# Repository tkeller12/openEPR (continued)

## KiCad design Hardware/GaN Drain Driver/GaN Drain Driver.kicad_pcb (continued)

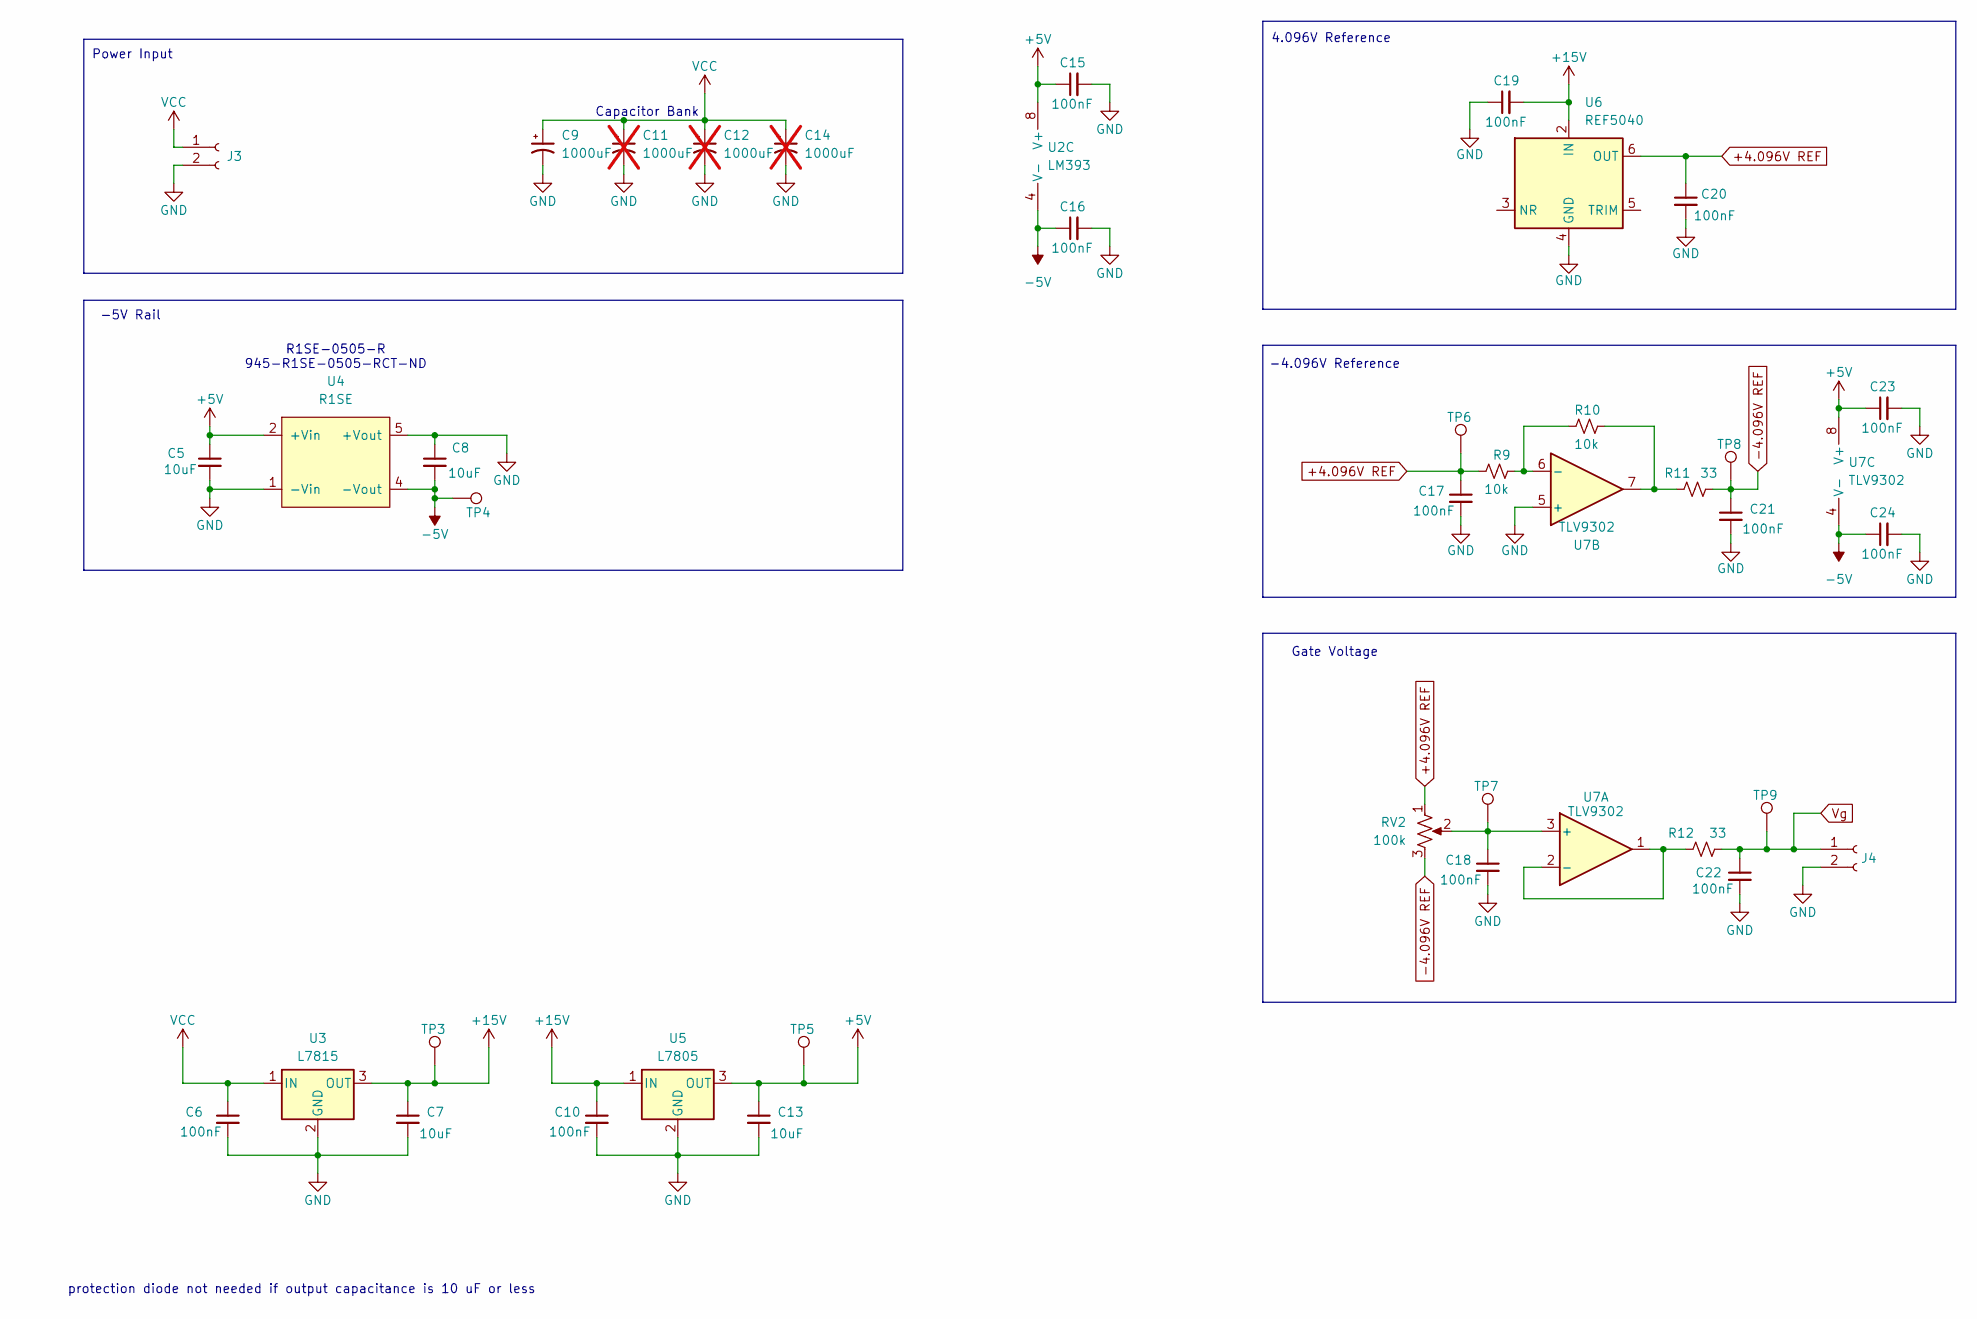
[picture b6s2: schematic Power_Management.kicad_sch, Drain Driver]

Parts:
C5, C7, C8, C13: 10uF; C_0805_2012Metric; MPN CL21A106KAYNNNE; Digikey 1276-2891-1-ND
C6, C10, C15, C16, C17, C18, C19, C20, C21, C22, C23, C24: 100nF; C_0805_2012Metric; MPN KGM21NR71H104KT; Digikey 478-KGM21NR71H104KTCT-ND
C9: 1000uF; CP_Radial_D13.0mm_P5.00mm; MPN UCY2C101MHD1TO; Digikey 493-4784-1-ND
C11, C12, C14: 1000uF; CP_Radial_D13.0mm_P5.00mm; MPN UCY2C101MHD1TO; Digikey 493-4784-1-ND; not fitted
J3, J4: 0022272021; Molex_KK-254_AE-6410-02A_1x02_P2.54mm_Vertical; MPN 0022272021; Digikey WM4111-ND
R9, R10: 10k; R_0805_2012Metric; MPN CRCW080510K0FKEAC; Digikey 541-3976-1-ND
R11, R12: 33; R_0805_2012Metric; MPN RC0805FR-0733RL; Digikey 311-33.0CRCT-ND
RV2: 100k; Potentiometer_Bourns_3296W_Vertical; MPN PV36W104C01B00; Digikey 118-PV36W104C01B00-ND
TP3, TP4, TP5, TP6, TP7, TP8, TP9: TestPoint; TestPoint_Pad_D1.0mm
U2: LM393; SOIC-8_3.9x4.9mm_P1.27mm; MPN LM393DT; Digikey 497-1593-1-ND
U3: L7815; TO-252-2; MPN MC78M15CDTG; Digikey MC78M15CDTGOS-ND
U4: R1SE; R1SE_SMD5_12.75X10.7X6.7_SINGLE_RCP; MPN R1SE-0505-R; Digikey 945-R1SE-0505-RCT-ND
U5: L7805; TO-252-2; MPN MC7805BDTRKG; Digikey MC7805BDTRKGOSCT-ND
U6: REF5040; SOIC-8_3.9x4.9mm_P1.27mm; MPN REF5040AIDR; Digikey 296-46190-1-ND
U7: TLV9302; SOIC-8_3.9x4.9mm_P1.27mm; MPN TLV9302IDR; Digikey 296-53513-1-ND

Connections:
+4.096V REF: C17.1, C20.1, R9.1, RV2.1, TP6.1, U6.6 (OUT); also elsewhere on the board
+5V: C5.1, C13.1, C15.1, C23.1, TP5.1, U2.8 (V+), U4.2 (+Vin), U5.3 (OUT), U7.8 (V+); also elsewhere on the board
+15V: C7.1, C10.1, C19.2, TP3.1, U3.3 (OUT), U5.1 (IN), U6.2 (IN); also elsewhere on the board
-4.096V REF: C21.1, R11.2, RV2.3, TP8.1; also elsewhere on the board
-5V: C8.2, C16.1, C24.1, TP4.1, U2.4 (V-), U4.4 (-Vout), U7.4 (V-)
GND: C5.2, C6.2, C7.2, C8.1, C9.2, C10.2, C11.2, C12.2, C13.2, C14.2, C15.2, C16.2, C17.2, C18.2, C19.1, C20.2, C21.2, C22.2, C23.2, C24.2, J3.2, J4.2, U3.2 (GND), U4.1 (-Vin), U4.5 (+Vout), U5.2 (GND), U6.4 (GND), U7.5 (+); also elsewhere on the board
unnamed: R10.2, R11.1, U7.7
unnamed: C18.1, RV2.2, TP7.1, U7.3 (+)
unnamed: R12.1, U7.1, U7.2 (-)
unnamed: R9.2, R10.1, U7.6 (-)
VCC: C6.1, C9.1, C11.1, C12.1, C14.1, J3.1, U3.1 (IN); also elsewhere on the board
Vg: C22.1, J4.1, R12.2, TP9.1; also elsewhere on the board

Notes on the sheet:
R1SE-0505-R 945-R1SE-0505-RCT-ND
protection diode not needed if output capacitance is 10 uF or less
-5V Rail
Gate Voltage
4.096V Reference
Capacitor Bank
Power Input
-4.096V Reference

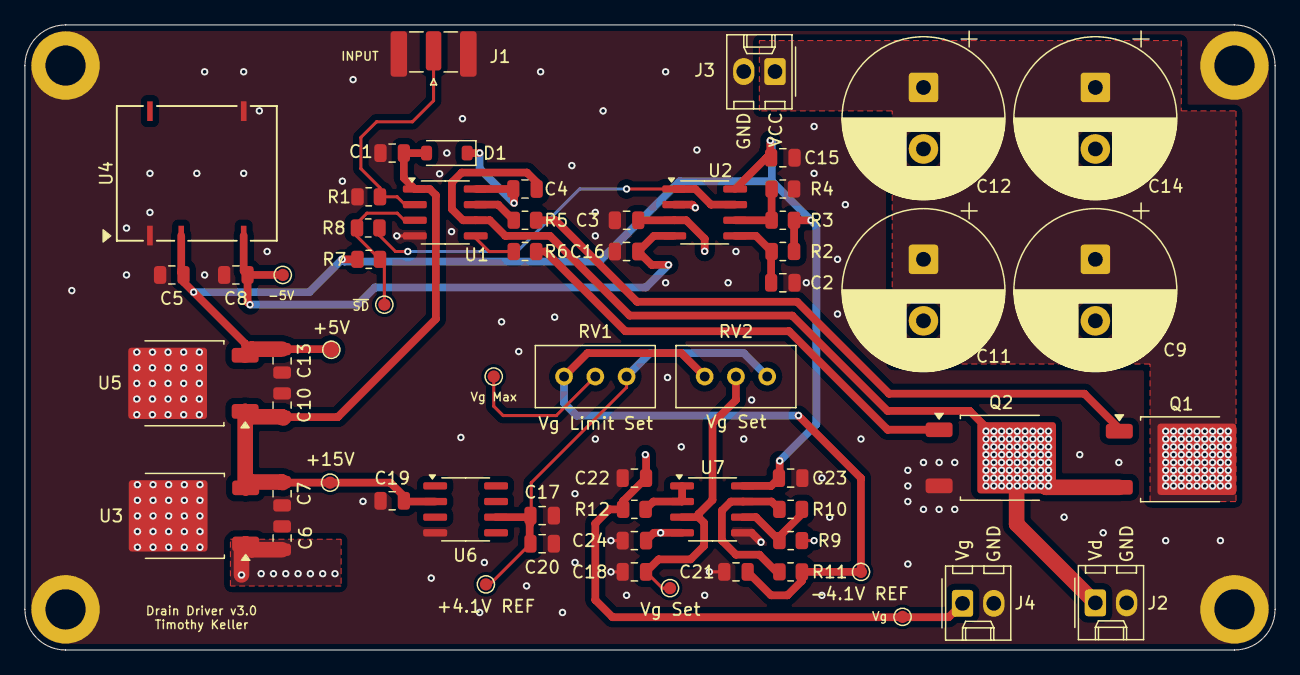
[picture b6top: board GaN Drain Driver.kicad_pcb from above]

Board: 4 copper layers, 101.6 x 50.8 mm, 65 parts (0 on the bottom side), 24 nets.

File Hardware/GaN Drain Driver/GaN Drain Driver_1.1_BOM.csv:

"Reference","Value","Footprint","Qty","DNP","Digikey","Manufacturer","MPN","Description"
"C1,C3,C4,C6,C10,C15,C16,C17,C18,C19,C20,C21,C22,C23,C24","100nF","Capacitor_SMD:C_0805_2012Metric","15","","478-KGM21NR71H104KTCT-ND","KYOCERA AVX","KGM21NR71H104KT","CAP CER 0.1UF 50V X7R 0805"
"C2,C5,C7,C8,C13","10uF","Capacitor_SMD:C_0805_2012Metric","5","","1276-2891-1-ND","Samsung Electro-Mechanics","CL21A106KAYNNNE","CAP CER 10UF 25V X5R 0805"
"C9","1000uF","Capacitor_THT:CP_Radial_D13.0mm_P5.00mm","1","","493-4784-1-ND","Nichicon","UCY2C101MHD1TO","CAP ALUM 100UF 20% 160V RADIAL"
"C11,C12,C14","1000uF","Capacitor_THT:CP_Radial_D13.0mm_P5.00mm","3","DNP","493-4784-1-ND","Nichicon","UCY2C101MHD1TO","CAP ALUM 100UF 20% 160V RADIAL"
"D1","1N5819HW-7-F","Diode_SMD:D_SOD-123","1","","1N5819HW-FDICT-ND","Diodes Incorporated","1N5819HW-7-F","DIODE SCHOTTKY 40V 1A SOD123"
"J1","SMA-J-P-H-ST-EM1","Connector_Coaxial:SMA_Samtec_SMA-J-P-X-ST-EM1_EdgeMount","1","","SAM8857-ND","Samtec Inc.","SMA-J-P-H-ST-EM1","CONN SMA JACK STR 50OHM EDGE MNT"
"J2,J3,J4","Conn_01x02_Socket","Connector_Molex:Molex_KK-254_AE-6410-02A_1x02_P2.54mm_Vertical","3","","WM4111-ND","Molex","0022272021","CONN HEADER VERT 2POS 2.54MM"
"Q1,Q2","NVD360N65S3T4G","Package_TO_SOT_SMD:TO-252-2","2","","488-NVD360N65S3T4GCT-ND","onsemi","NVD360N65S3T4G","SF3 EASY AUTO 360MOHM DPAK"
"R1,R2,R3,R4,R7,R9,R10","10k","Resistor_SMD:R_0805_2012Metric","7","","541-3976-1-ND","Vishay Dale","CRCW080510K0FKEAC","RES 10K OHM 1% 1/8W 0805"
"R5,R6,R11,R12","33","Resistor_SMD:R_0805_2012Metric","4","","311-33.0CRCT-ND","YAGEO","RC0805FR-0733RL","RES 33 OHM 1% 1/8W 0805"
"RV1,RV2","100k","Potentiometer_THT:Potentiometer_Bourns_3296W_Vertical","2","","118-PV36W104C01B00-ND","Bourns Inc.","PV36W104C01B00","TRIMMER 100K OHM 0.5W PC PIN TOP"
"U1","IRS2008S","Package_SO:SOIC-8_3.9x4.9mm_P1.27mm","1","","IRS2008STRPBFCT-ND","Infineon Technologies","IRS2008STRPBF","IC GATE DRVR HALF-BRIDGE 8SOIC"
"U2","LM393","Package_SO:SOIC-8_3.9x4.9mm_P1.27mm","1","","497-1593-1-ND","STMicroelectronics","LM393DT","IC COMPARATOR 2 GEN PUR 8SOIC"
"U3","L7815","Package_TO_SOT_SMD:TO-252-2","1","","MC78M15CDTGOS-ND","onsemi","MC78M15CDTG","IC REG LINEAR 15V 500MA DPAK"
"U4","R1SE","_tim-DC-DC:R1SE_SMD5_12.75X10.7X6.7_SINGLE_RCP","1","","945-R1SE-0505-RCT-ND","Recom Power","R1SE-0505-R","DC DC CONVERTER 5V 1W"
"U5","L7805","Package_TO_SOT_SMD:TO-252-2","1","","MC7805BDTRKGOSCT-ND","onsemi","MC7805BDTRKG","IC REG LINEAR 5V 1A DPAK"
"U6","REF5040","Package_SO:SOIC-8_3.9x4.9mm_P1.27mm","1","","296-46190-1-ND","Texas Instruments","REF5040AIDR","IC VREF SERIES 0.1% 8SOIC"
"U7","TLV9302","Package_SO:SOIC-8_3.9x4.9mm_P1.27mm","1","","296-53513-1-ND","Texas Instruments","TLV9302IDR","Dual Low-Voltage Rail-to-Rail Output Operational Amplifiers, SOIC-8/SSOP-8"

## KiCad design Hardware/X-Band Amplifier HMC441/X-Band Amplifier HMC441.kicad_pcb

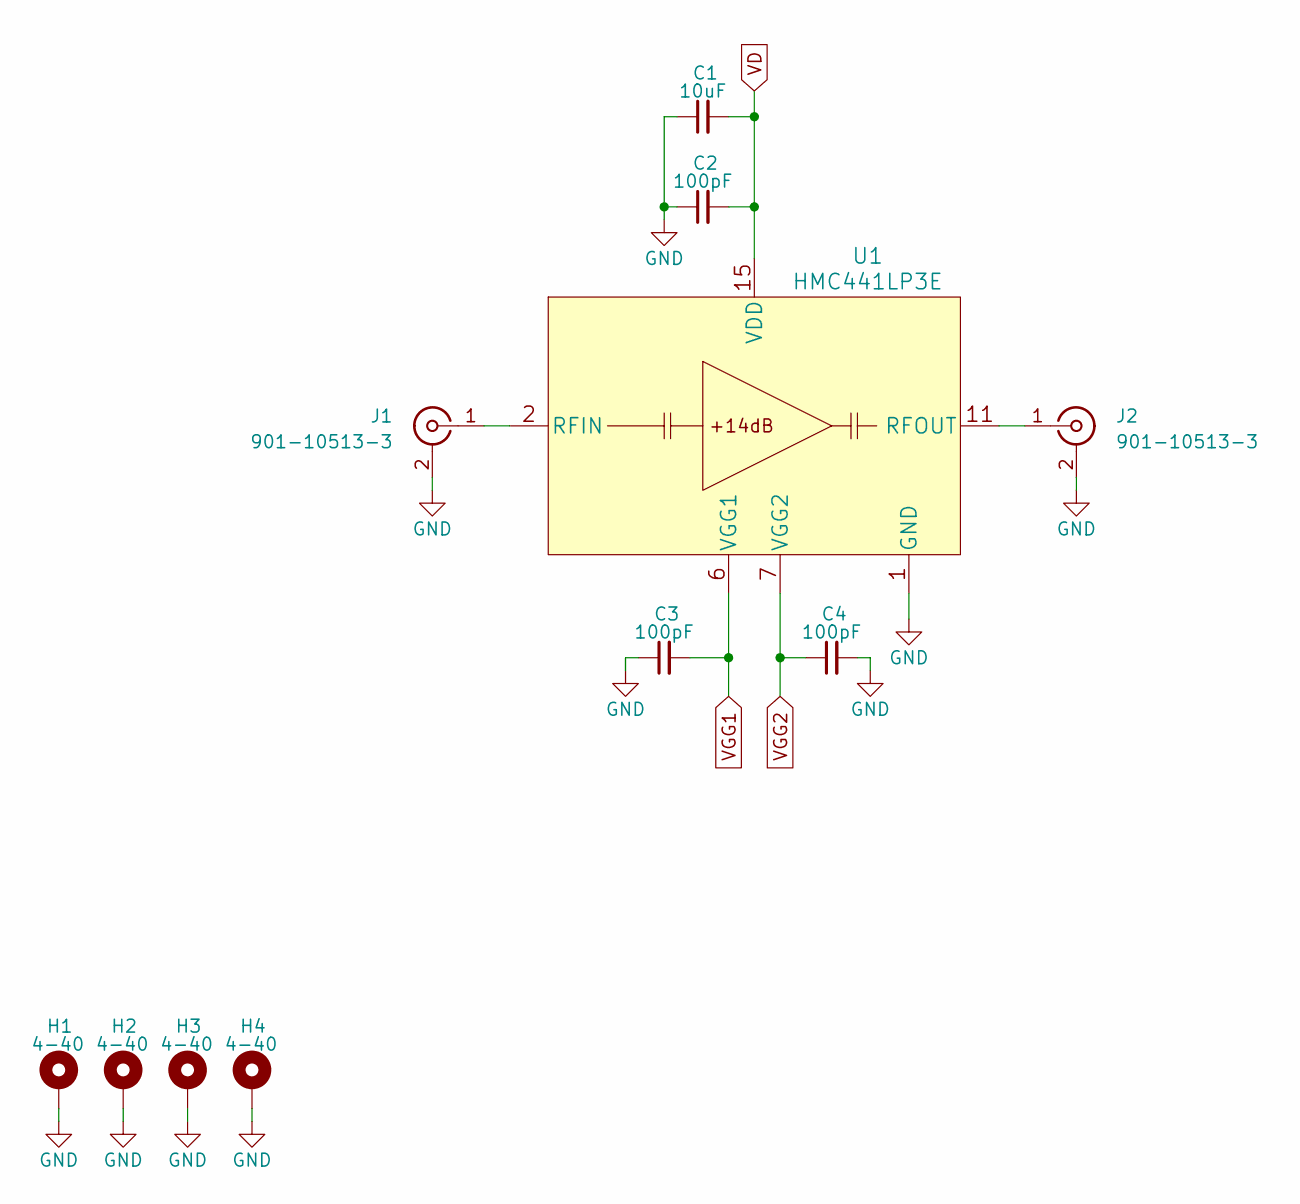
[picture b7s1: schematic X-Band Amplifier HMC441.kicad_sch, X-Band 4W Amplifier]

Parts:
C1: 10uF; C_0805_2012Metric
C2, C3, C4: 100pF; C_0402_1005Metric
H1, H2, H3, H4: 4-40; 4-40_Hole_Pad
J1, J2: 901-10513-3; AMPHENOL_901-10513-3_EDGE_LAUNCH_Female
U1: HMC441LP3E; HMC441LP3ETR

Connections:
GND: C1.1, C2.1, C3.1, C4.2, H1.1, H2.1, H3.1, H4.1, J1.2 (Ext), J2.2 (Ext), U1.1 (GND), U1.3 (GND), U1.4 (GND), U1.5 (GND), U1.8 (GND), U1.9 (GND), U1.10 (GND), U1.12 (GND), U1.13 (GND), U1.14 (GND), U1.16 (GND), U1.17 (GND)
unnamed: J1.1 (In), U1.2 (RFIN)
unnamed: J2.1 (In), U1.11 (RFOUT)
VD: C1.2, C2.2, U1.15 (VDD)
VGG1: C3.2, U1.6 (VGG1)
VGG2: C4.1, U1.7 (VGG2)

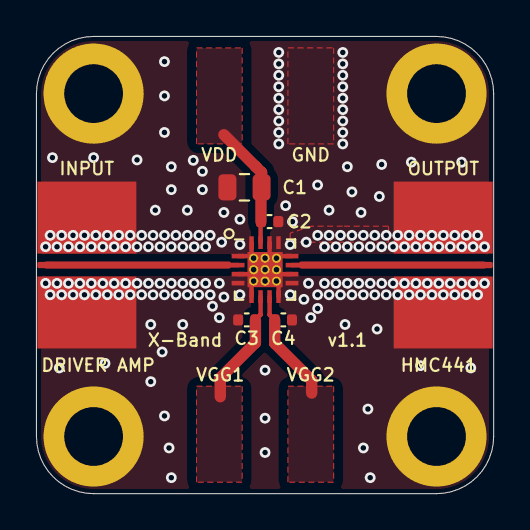
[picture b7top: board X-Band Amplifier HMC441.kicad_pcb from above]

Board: 4 copper layers, 25.4 x 25.4 mm, 11 parts (0 on the bottom side), 6 nets.

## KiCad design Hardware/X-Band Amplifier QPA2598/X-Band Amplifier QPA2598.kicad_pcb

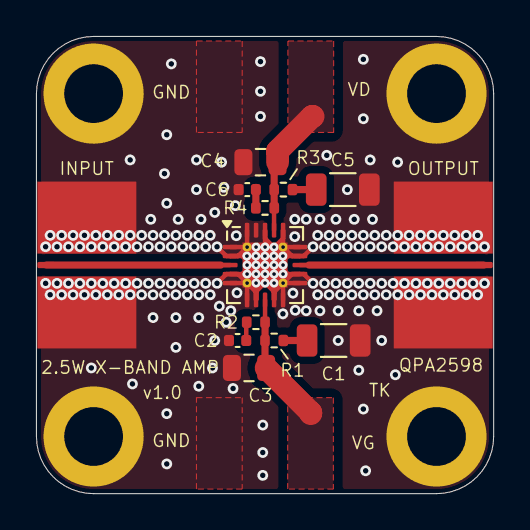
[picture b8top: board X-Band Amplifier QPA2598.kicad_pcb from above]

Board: 4 copper layers, 25.4 x 25.4 mm, 17 parts (0 on the bottom side), 9 nets.

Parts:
C1, C5: 10uF; C_1206_3216Metric
C2, C6: 1nF; C_0402_1005Metric
C3, C4: 10uF; C_0805_2012Metric
H1, H2, H3, H4: 4-40; 4-40_Hole_Pad
J1, J2: 901-10513-3; AMPHENOL_901-10513-3_EDGE_LAUNCH_Female
R1, R3: 0; R_0402_1005Metric
R2, R4: 1.8; R_0402_1005Metric
U1: QPA2598; QFN-20-1EP_4x4mm_P0.5mm_EP2.5x2.5mm_ThermalVias

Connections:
GND: C1.1, C2.1, C3.1, C4.2, C5.2, C6.2, H1.1, H2.1, H3.1, H4.1, J1.2 (Ext), J2.2 (Ext), U1.1 (NC), U1.2 (NC), U1.4 (NC), U1.5 (NC), U1.6 (NC), U1.7 (NC), U1.9 (NC), U1.10 (NC), U1.11 (NC), U1.12 (NC), U1.14 (NC), U1.15 (NC), U1.16 (NC), U1.18 (NC), U1.19 (NC), U1.20 (NC), U1.21 (GND)
unnamed: C1.2, R1.1
unnamed: C2.2, R2.1
unnamed: C5.1, R3.2
unnamed: C6.1, R4.2
unnamed: J1.1 (In), U1.3 (RF_IN)
unnamed: J2.1 (In), U1.13 (RF_OUT)
VD: C4.1, R3.1, R4.1, U1.17 (VD)
VG: C3.2, R1.2, R2.2, U1.8 (VG)

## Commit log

2023-05-21 Adding KiCAD project for L-Band Bridge
2023-05-21 Updating L-Band Bridge Schematic
2023-05-27 Updates to L-Band Bridge
2023-05-29 Backups
2023-06-03 L-Band Bridge Schematic Updates
    Assigning footprints
2023-06-03 Adding gitignore
2023-06-03 Starting development of GUI for acquisition
2023-06-12 Updating Schematic
    Removed Power Divider
    Removed Op Amp on IF output
2023-07-30 Removing Filter and IF Amp
2023-07-30 Working on BOM
2023-08-19 Creating new schematic for S-band transceiver
2023-08-20 Added receiver bypass switch comment
2024-02-17 Adding notes to S-band transceiver
2024-03-01 Updates to Schematic
2024-03-02 Working on schematic for adf4351
2024-03-03 Updating schematic
2024-03-05 Updates to receiver
2024-03-06 Updates to power supply schematic
2024-03-07 Changes to schematic
2024-03-12 Updating microcontroller schematic
2024-03-13 Updating PLL
2024-03-16 Finished assigning footprints and starting board layout
2024-03-16 Fixed issue with limiter footprint
2024-03-16 Updating Capacitors and LEDs in schematic
2024-03-16 Updating synthesizer schematic and layout
2024-03-16 Updates to synthesizer layout
2024-03-16 Updating board layout, adding inductor to LNA input
2024-03-17 Starting to route board
2024-03-17 Routing board
2024-03-17 Updating board layout and routing
2024-03-17 Routing microcontroller
2024-03-17 Updating routing
2024-03-17 Updating silkscreen
2024-03-17 Cleaning up silkscreen
2024-03-17 Removing solder mask from coplanar waveguide traces
2024-03-17 Updates to Board
2024-03-18 Updating notes in schematic
2024-03-18 Adding gerbers for v1.0
2024-03-18 Minor Changes
2024-03-19 Updates to BOM
2024-03-23 Adding firmware for S-Band Transceiver
2024-03-23 Adding library files
2024-03-24 updating values
2024-03-24 Updating BOM
2024-03-24 Adding ADC library and serial commands
2024-03-24 Updating platform io settings
2024-03-24 Adding library for digital phase shifter
2024-03-24 Cleaning up code
2024-03-25 Fixing bug in firmware with TX and RX Amp enable
2024-03-26 Fixing bug with RUN LED
2024-03-26 Fixed bug with ADC readings
    Need to remove TX AMP Enable
2024-03-26 Defined RUN LED delay
2024-03-26 Updating python script
2024-03-26 Testing manually setting PIN_B5 to output
2024-03-26 updating frequency range of sweep default values
2024-03-26 Fixing issues in schematic
2024-03-26 Fixed issue with tx amp enable added new serial commands
2024-03-27 Fixing issue with phase shifter schematic
2024-03-27 Minor change to script
2024-03-28 Adding serial command for lock detect
2024-03-28 minor changes to script
2024-03-30 Updating SPI mode for Phase shifter IC
2024-03-30 Updating python phase function
2024-03-30 Creating python package for controlling S-band transceiver
2024-03-31 Adding new script for tuning
2024-04-04 Adding bridge controller schematic
2024-04-05 Updating bridge controller
2024-04-06 Updates to Bridge controller
2024-04-15 Updating DAQ
2024-04-18 Updates to DAQ board layout
2024-04-19 Fixed DRC errors on Board
2024-04-19 Need to update TX/RX level for UART communication
2024-04-19 Updating FTDI controller for +5V RX and TX
2024-04-19 Finalizing Board Routing
2024-04-20 Minor Updates to Board
2024-04-20 Adding gerbers
2024-04-25 Adding S-Band Amplifier project
2024-04-27 Updating Amplifier board
2024-04-27 Finalizing Amplifier Board
2024-04-28 Adding gerbers for S-band amplifier
2024-05-01 Fixing issue with Silkscreen on PCB
2024-05-01 Incrementing Board Version
2024-05-02 Updating tune script
2024-05-02 Auto stash before merge of "master" and "origin/master"
2024-05-02 Updating DAQ board schematic
2024-05-02 Updates to DAQ
2024-05-02 Adding CAD model for PCB and heat spreader
2024-05-05 Adding S-Band Driver Amplifier
2024-05-05 Updating Schematic and Board
2024-05-05 Generated Gerbers for S-Band Driver Amp
2024-05-09 Updating script to set parameters
2024-05-09 Adding decoupling capacitor
2024-05-10 adding calibration script
2024-05-10 Adding script for calibration data
2024-05-12 adding new project for PFU
2024-05-14 Updating schematic for PFU
2024-06-04 Updating parameters setting script
2024-06-04 Adding phase function WIP
2024-06-04 Testing phase, not currently working
2024-06-04 Testing divided feedback
2024-06-04 more testing...
2024-06-04 Working example
    register 5 must be 0x5A0005
2024-06-07 Testing parameters
2024-06-09 Adding instrument server
2024-06-09 testing server class
2024-06-16 Creating X-Band Amplifier Project
2024-06-16 Updating Board
2024-06-16 Updated Board
2024-06-16 Adding capacitors
2024-06-16 Adding GaN gate driver
2024-06-18 Updates to gate driver
2024-06-18 Adding drain driver project
2024-06-18 updates to schematic for drain driver
2024-06-19 Started drain driver board
2024-06-19 Updating drain driver board
2024-06-20 Updated drain driver PCB
2024-06-20 Added capacitors
2024-06-20 Adding STEP file
2024-06-21 Updating gate driver board
2024-06-21 Working on gate driver board
2024-06-21 Updating board layout
2024-06-21 Updated PCB
2024-06-29 Adding QPA2598 Amplifier PCB
2024-06-29 Adding Gerber files
2024-06-30 Updating Drain Driver PCB
2024-07-09 Adding new 10 MHz ref
2024-07-12 Updating GaN driver
2024-07-13 working on board layout
2024-07-13 Updating QPA1022 amplifier
2024-07-13 Updating 4W amplifier, creating gerbers
2024-07-16 10 MHz ref docs
2024-07-16 Updating 10 MHz reference schematic
2024-07-24 Fixing issue with reference
2024-07-26 Adding X-band driver amplifier
2024-09-11 Adding AFC project
2024-09-12 Updating Schematic for AFC
2024-09-13 Updating Schematic for AFC Circuit
2024-09-14 Updates to AFC schematic
2024-09-15 Adding filter to schematic
2024-09-16 Adding amplifier
2024-09-16 Updating resistor values in filter
2024-09-16 Adding low noise instrumentation amplifier to conventional AFC input
2024-09-17 Adding VCO schematic
2024-09-17 Changing to low noise op amp
2024-09-21 Adding sheets to schematic and starting PID controller
2025-07-05 Updating drain driver
2025-07-06 Updates to Drain Driver
2025-07-06 Adding simple PFU
2025-07-07 Generating Gerbers for PFU
2025-07-08 Updating Drain Driver, Consolidating BOM
2025-07-09 Adding BOM, Fixing schematic issue
2025-07-09 Updating SMA footprint
2025-07-09 Running DRC on PCB
2025-07-10 Updating fab layer of PCB
2025-07-10 Creating assembly print
2025-07-11 fixed switch
2025-07-12 Adding gerbers and bom for gate driver
2025-07-12 Adding circulator kicad project
2025-07-17 Adding S-Band Limiter design
2025-07-20 Adding S-band LGR KiCAD Project
2025-07-20 Updating pytxr and adding GUI
2025-07-21 Updates to GUI
2025-07-25 Improving pytxr initialization of serial port
2025-07-25 BOM script
2025-07-27 Adding New S-band LGR Void project
2025-07-27 Updates to LGR Void
2025-07-27 Adding BOM
2026-01-11 Adding 150 MHz phase shifter schematic
2026-01-11 Working on Board layout for 150 MHz phase shifter
2026-02-01 Phase shifter backups
2026-02-01 Adding low noise preamp schematic
2026-02-01 Adding Low Noise Pre-Amp board
2026-02-02 Finalizing board layout
2026-02-03 Minor changes to Pre amp
2026-02-10 Creating excel BOM file
2026-04-25 adding script to sweep frequency and phase while tuning
2026-04-27 Adding notes to schematic
